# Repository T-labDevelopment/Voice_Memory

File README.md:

# Voice_Memory — 主開発：ESP32 T-Display Rev.A

**2026-11-25時点の主開発対象はESP32 T-Display 16MB版。** CH32V003 v1/v2は履歴として保持します。設計世代や製造用スナップショットは上書きせず区別します。

- [2026-11-25 00:46 Gerber受領・差し替え確認（PCB(2).zipを発注用正本とする）](releases/esp32-tdisplay-orderfiles-check-2026-11-25/ORDER_STATUS_JA.md)
- [2026-11-25 00:39 KiCad設計正本](hardware/source-archives/tdisplay-order-candidate-2026-11-25/VoiceMemory_TDisplay-2026-11-25_003943.zip)
- [2026-11-24 23:41 発注前GPIO検証版](releases/esp32-tdisplay-preorder-pin-audit-2026-11-24/README.md)
- [2026-11-24 旧Prototype発注データ](releases/esp32-tdisplay-prototype-ordered-2026-11-24/README.md)
- [旧CH32V003版の製造履歴](releases/v2-manufacturing-approved-2026-11-11/README.md)

**発注用Gerber正本：** [PCB(2).zip](hardware/source-archives/tdisplay-order-candidate-2026-11-25/PCB(2).zip)（SHA-256は[検査記録](releases/esp32-tdisplay-orderfiles-check-2026-11-25/GERBER_MANIFEST_2026-11-25.json)に記載）。前に受領した `PCB(1).zip` は空であり**使用禁止**。

**2026-11-25 00:56:43 JSTのJLCPCB注文画面で、PCB 5枚・基板代US$2.00・送料US$1.00・合計US$3.00の「支払い済み」および「レビュー」工程を確認。** 基板厚1.2mmはユーザー指定の注文条件で、画像単独では独立照合できません。注文番号は公開リポジトリに掲載しません。KiCad設計ファイルやGerberそのものの厚み設定は変更していません。基板認識寸法はGerberジョブファイル上80.06×100.05mmであり、見積価格・CAM外形・取付穴は注文画面で確認してください。

Git作業ブランチで管理し、`main`へは指示なく統合しません。

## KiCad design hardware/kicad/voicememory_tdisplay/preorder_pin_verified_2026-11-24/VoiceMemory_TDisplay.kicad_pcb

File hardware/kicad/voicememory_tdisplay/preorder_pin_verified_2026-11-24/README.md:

# ESP32 T-Display Rev.A — 2026-11-24 23:41 発注準備版

**User-supplied exact source:** `VoiceMemory_TDisplay-2026-11-24_234138.zip`。

- 状態：発注前GPIO・フットプリント照合済み、外形80.01 × 100.00 mm。基板設計はユーザー修正済み。
- ERC(4).rpt：2026-11-24 23:09 エラー0 / 警告0。
- DRC(2).rpt：2026-11-24 23:41 違反0 / 未接続0 / FPエラー0。
- [24ピン監査と注意事項](PIN_AUDIT_2026-11-24_JA.md)、[ピンごとのCSV](MODULE_PINMAP_AUDIT_2026-11-24.csv)。
- 既存KiCad配置・回路・配線は変更しない。自動保存・個人設定`*.kicad_prl`は作業ディレクトリから除外。
- メーカーPinout照合はLILYGO初代T-Display V1.1を基準とする。TENSTAR16MB版の実品電源ルートおよびピン互換性は購入現物の照合事項。
- 過去版`PCB.zip` は使わず、このPCBからGerber/ドリルを新規出力する。

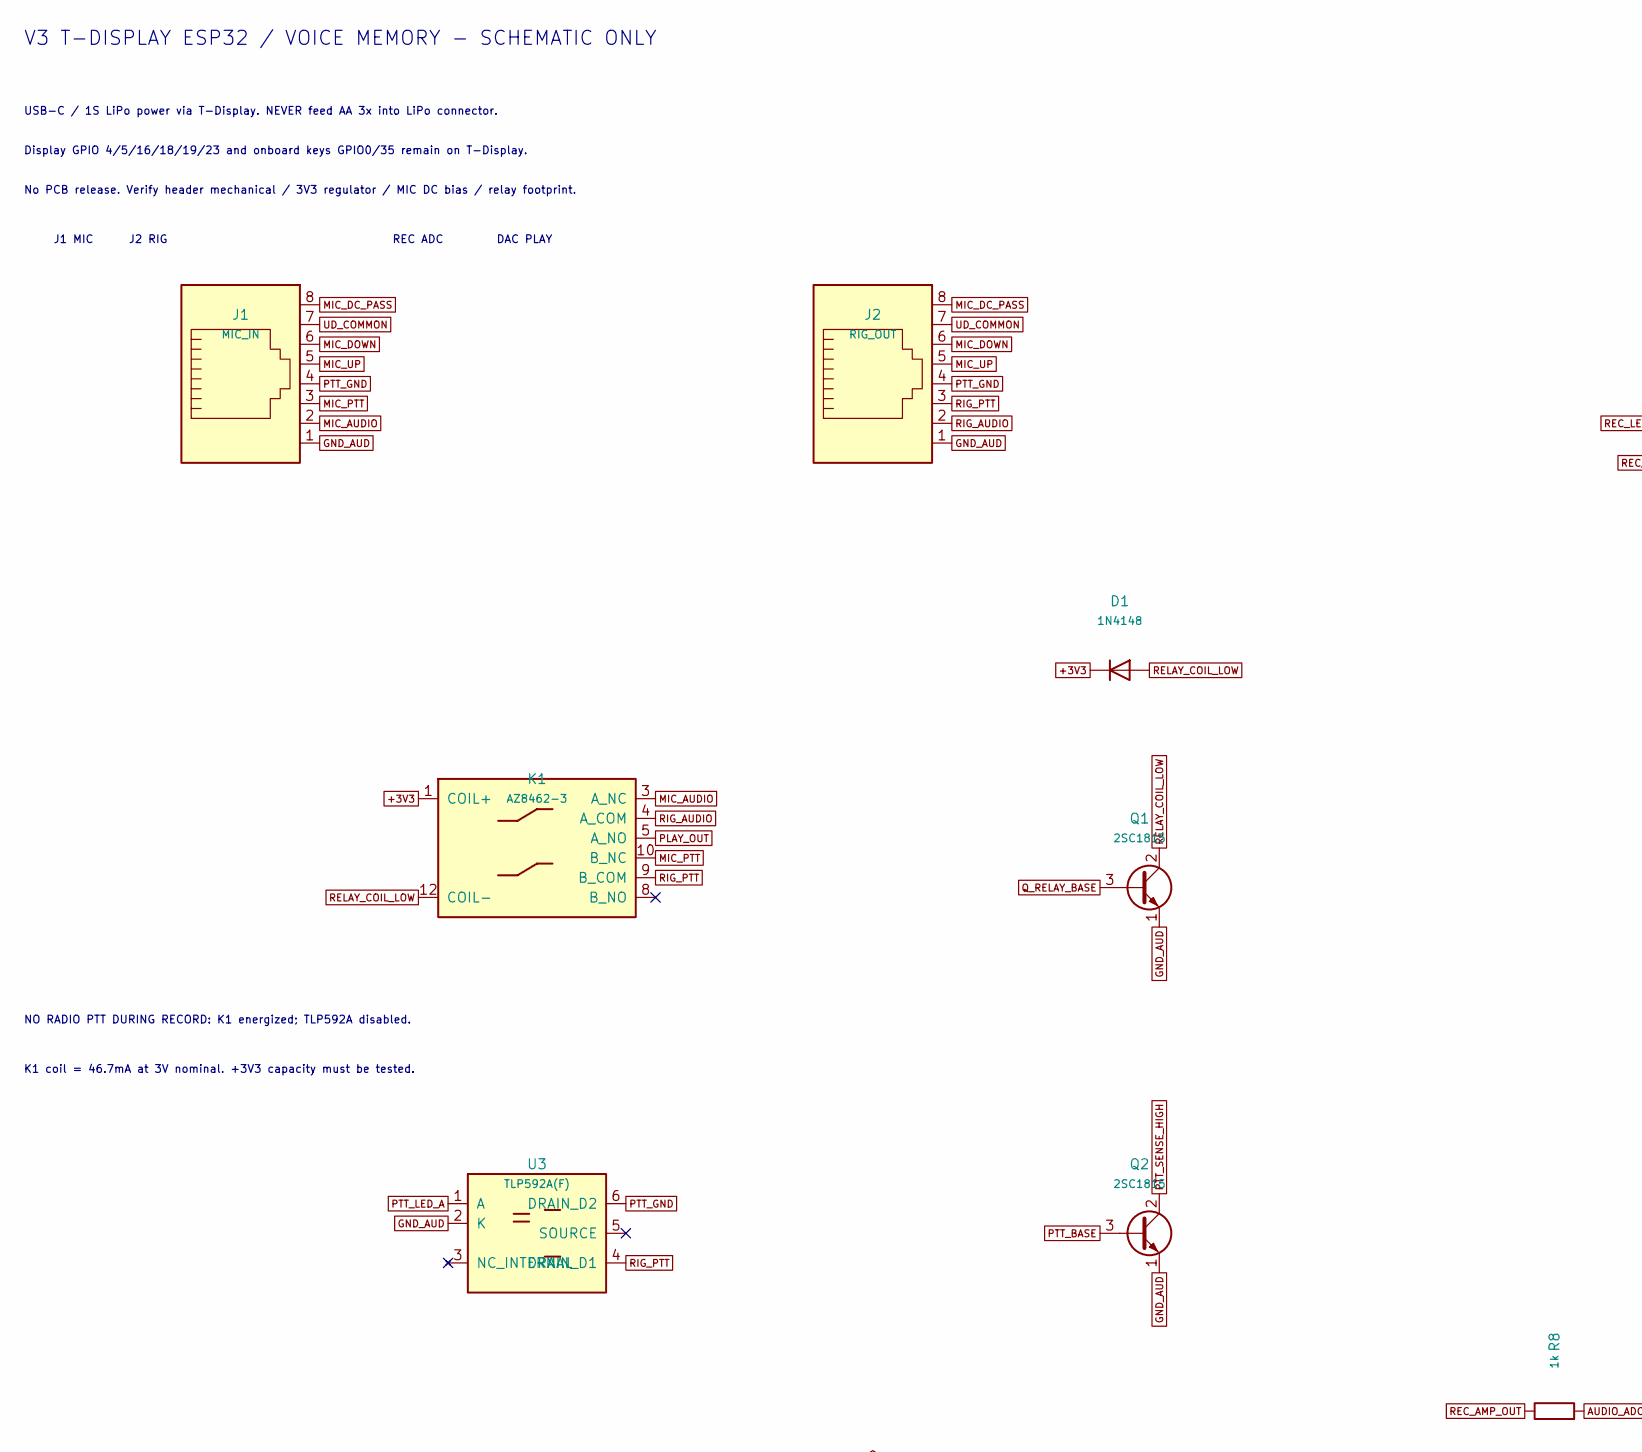
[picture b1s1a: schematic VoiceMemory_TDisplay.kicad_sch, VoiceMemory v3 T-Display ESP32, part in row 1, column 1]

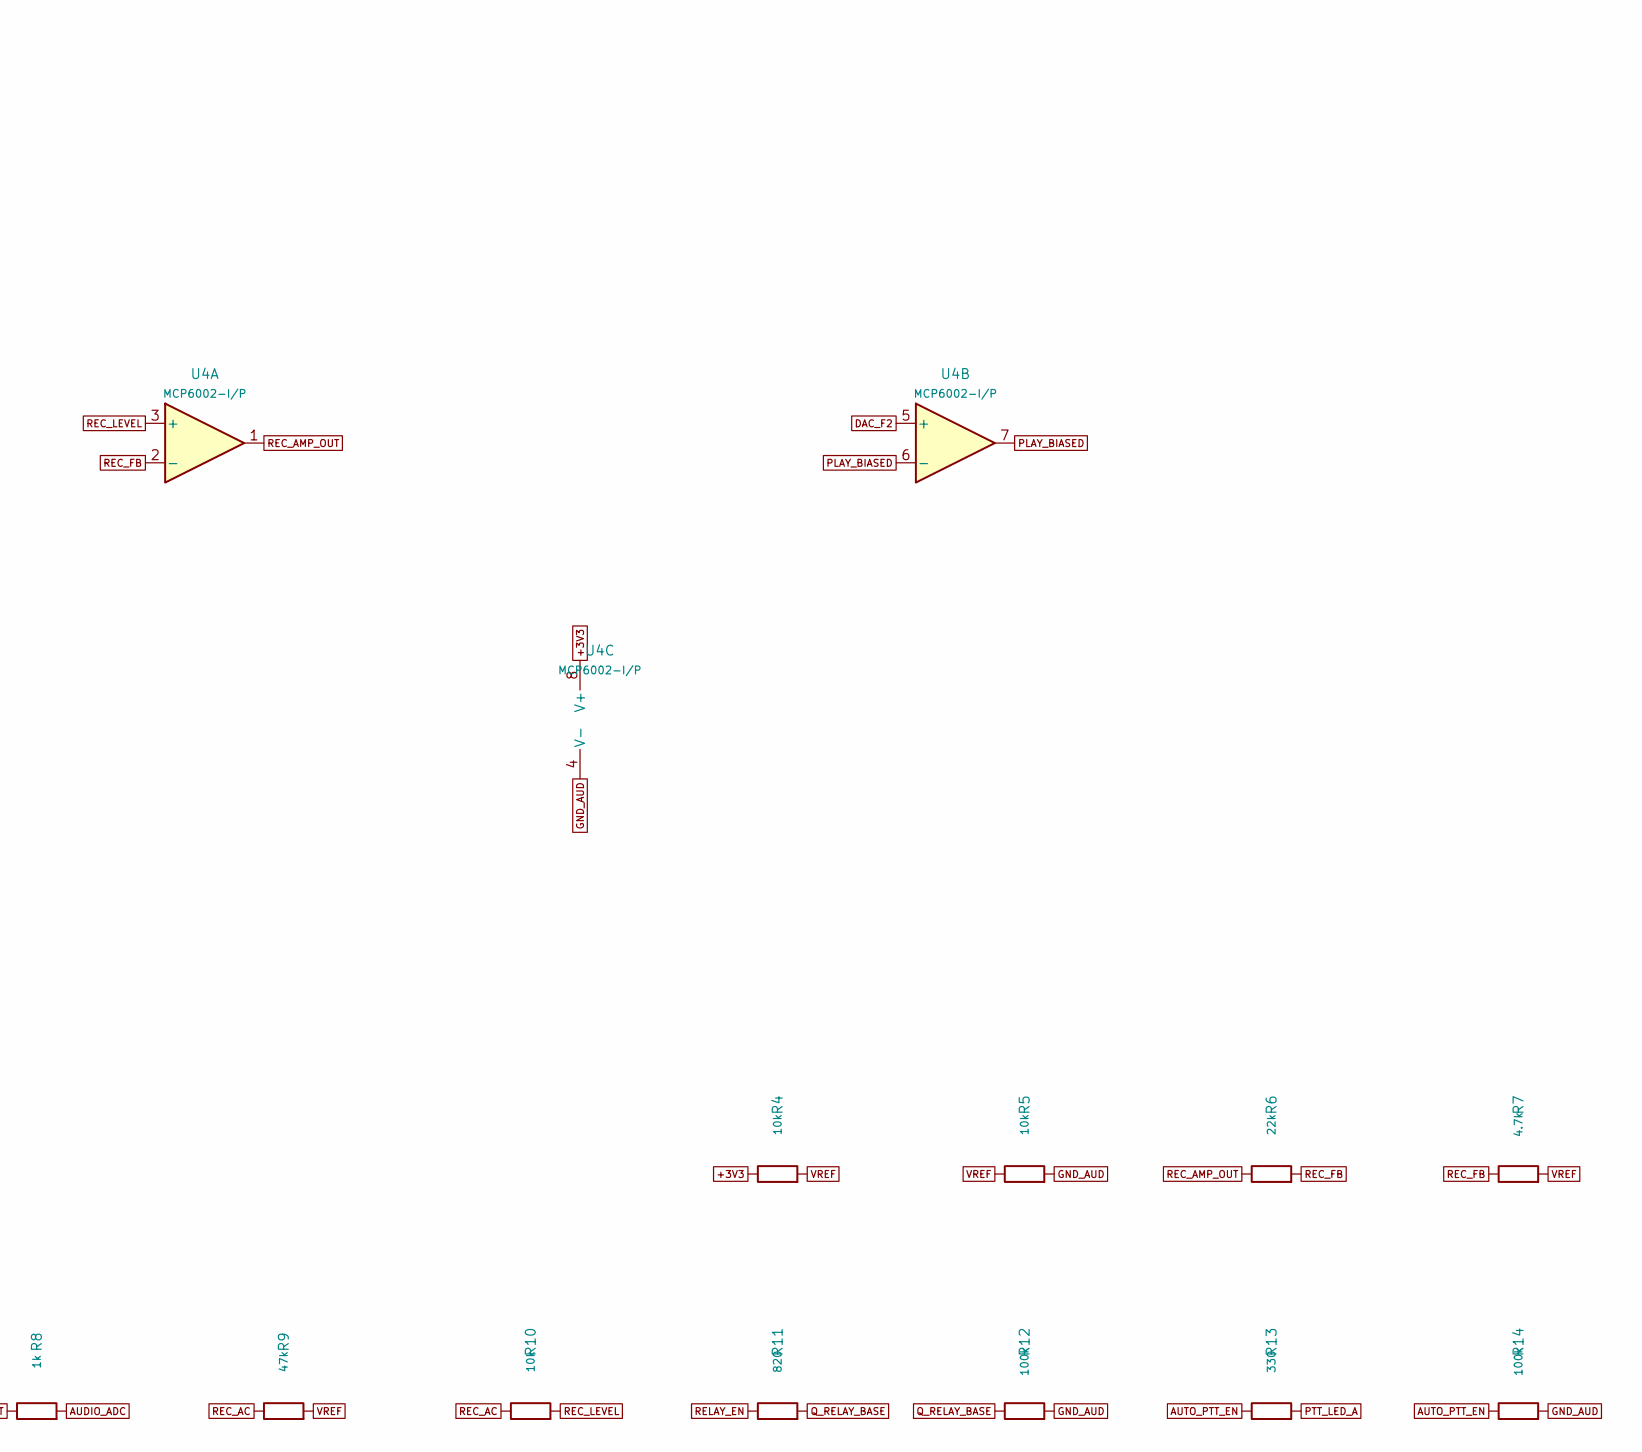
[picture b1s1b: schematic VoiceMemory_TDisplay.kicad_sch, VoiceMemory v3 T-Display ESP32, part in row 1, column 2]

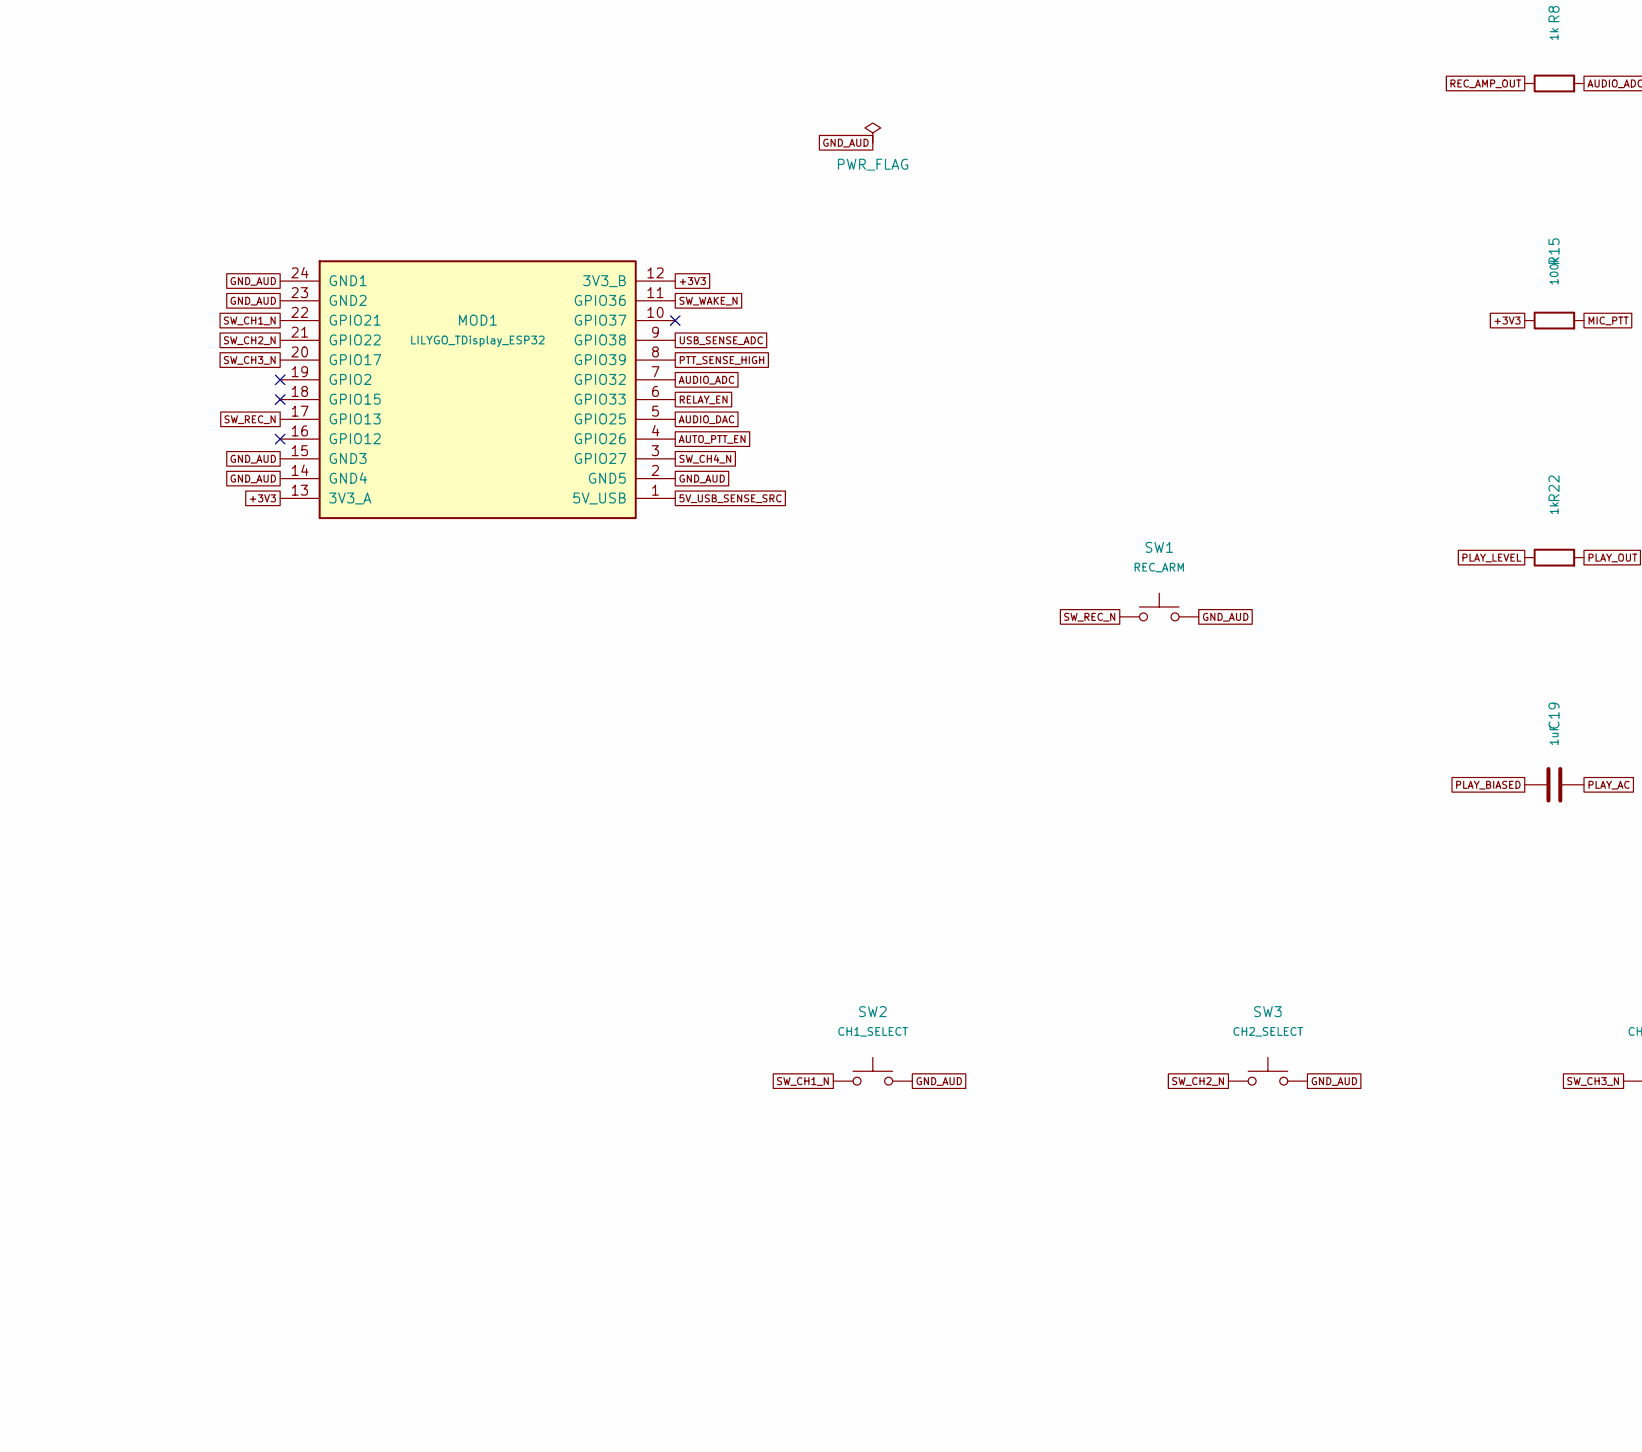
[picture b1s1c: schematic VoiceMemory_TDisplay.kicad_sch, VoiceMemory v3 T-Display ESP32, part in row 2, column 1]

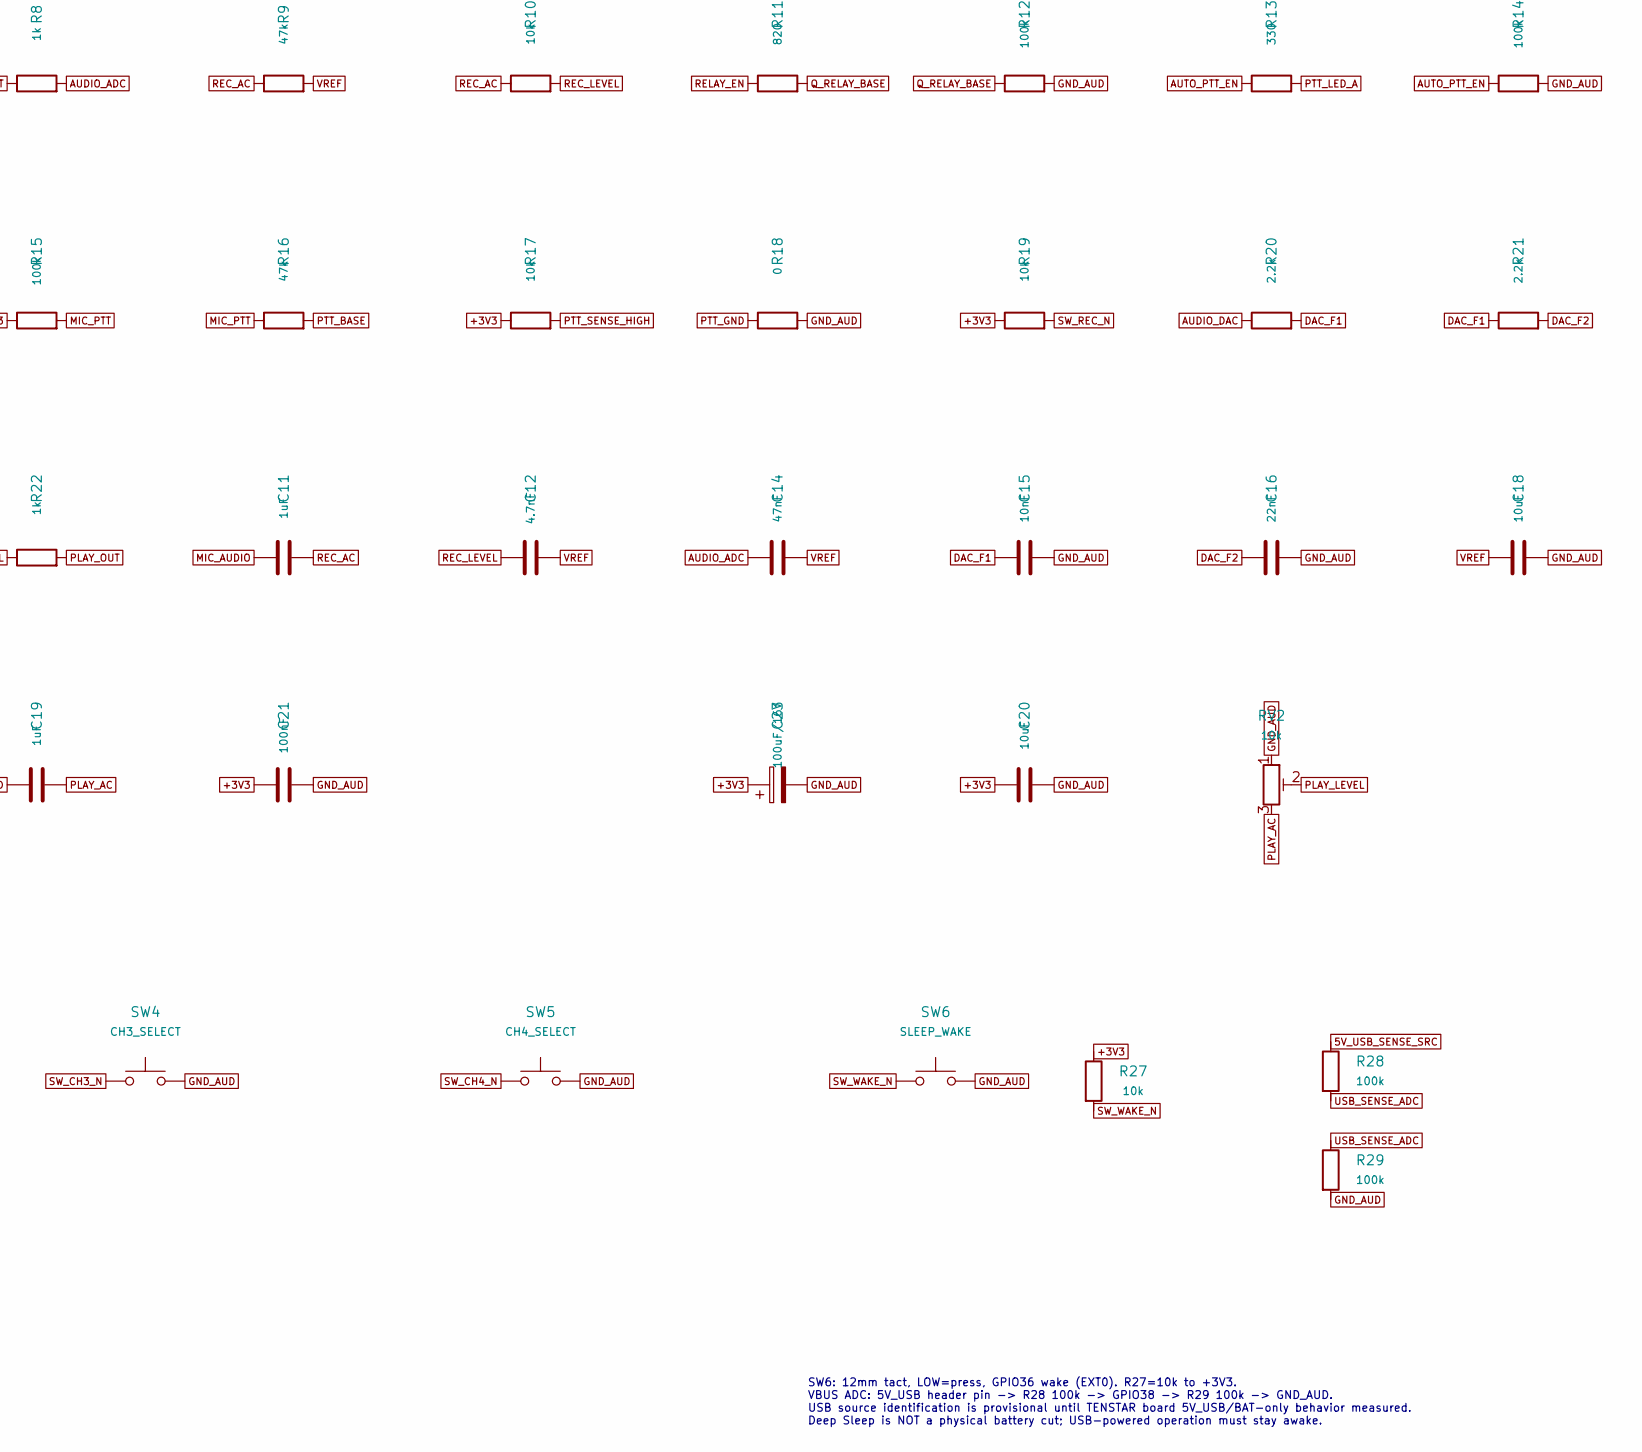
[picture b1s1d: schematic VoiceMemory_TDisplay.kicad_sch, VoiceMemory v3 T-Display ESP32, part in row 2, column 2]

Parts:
C11, C19: 1uF; C_1206_3216Metric; Manufacturer Part Number 25MU105MA23216
C12: 4.7nF; C_0805_2012Metric; Tolerance ±5%; Manufacturer Part Number GRM2195C1H472JA01D
C14: 47nF; C_0805_2012Metric; Tolerance ±5%; Manufacturer Part Number GRM2191X1A473JA01D
C15: 10nF; C_0805_2012Metric; Tolerance ±5%; Manufacturer Part Number GRM2195C1H103JA01D
C16: 22nF; C_0805_2012Metric; Tolerance ±5%; Manufacturer Part Number GRM21B5C1H223JA01L
C18, C20: 10uF; C_0805_2012Metric; Tolerance ±10%; Manufacturer Part Number CL21A106KOQNNNE
C21: 100nF; C_0805_2012Metric; Tolerance ±5%; Manufacturer Part Number GRM21B1X1A104JA01L
C23: 100uF/16V; CP_Radial_D5.0mm_P2.00mm; Tolerance ±20%; Manufacturer Part Number 16PX100MEFC5X11
D1: 1N4148; D_SOD-123
J1: MIC_IN; RJ45_8P8C_THT_15.91x15.10
J2: RIG_OUT; RJ45_8P8C_THT_15.91x15.10
K1: AZ8462-3; Relay_Zettler_AZ8462_DIP8
MOD1: LILYGO_TDisplay_ESP32; TTGO-T-Display
Q1, Q2: 2SC1815; TO-92_Inline
R4, R5, R10, R17, R19, R27: 10k; R_0805_2012Metric
R6: 22k; R_0805_2012Metric
R7: 4.7k; R_0805_2012Metric
R8, R22: 1k; R_0805_2012Metric
R9, R16: 47k; R_0805_2012Metric
R11: 820; R_0805_2012Metric
R12, R14, R15, R28, R29: 100k; R_0805_2012Metric
R13: 330; R_0805_2012Metric
R18: 0; R_0805_2012Metric
R20, R21: 2.2k; R_0805_2012Metric
RV2: 10k; Potentiometer_Runtron_RM-065_Vertical
SW1: REC_ARM; SW_PUSH-12mm
SW2: CH1_SELECT; SW_PUSH-12mm
SW3: CH2_SELECT; SW_PUSH-12mm
SW4: CH3_SELECT; SW_PUSH-12mm
SW5: CH4_SELECT; SW_PUSH-12mm
SW6: SLEEP_WAKE; SW_PUSH-12mm
U3: TLP592A(F); DIP-6_W7.62mm
U4: MCP6002-I/P; DIP-8_W7.62mm

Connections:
5V_USB_SENSE_SRC: MOD1.1 (5V_USB), R28.1
+3V3: C20.1, C21.1, C23.1, D1.1 (K), K1.1 (COIL+), MOD1.12 (3V3_B), MOD1.13 (3V3_A), R4.1, R15.1, R17.1, R19.1, R27.1, U4.8 (V+)
AUDIO_ADC: C14.1, MOD1.7 (GPIO32), R8.2
AUDIO_DAC: MOD1.5 (GPIO25), R20.1
AUTO_PTT_EN: MOD1.4 (GPIO26), R13.1, R14.1
DAC_F1: C15.1, R20.2, R21.1
DAC_F2: C16.1, R21.2, U4.5 (+)
GND_AUD: C15.2, C16.2, C18.2, C20.2, C21.2, C23.2, J1.1, J2.1, MOD1.2 (GND5), MOD1.14 (GND4), MOD1.15 (GND3), MOD1.23 (GND2), MOD1.24 (GND1), Q1.1 (E), Q2.1 (E), R5.2, R12.2, R14.2, R18.2, R29.2, RV2.1, SW1.2, SW2.2, SW3.2, SW4.2, SW5.2, SW6.2, U3.2 (K), U4.4 (V-)
MIC_AUDIO: C11.1, J1.2, K1.3 (A_NC)
MIC_DC_PASS: J1.8, J2.8
MIC_DOWN: J1.6, J2.6
MIC_PTT: J1.3, K1.10 (B_NC), R15.2, R16.1
MIC_UP: J1.5, J2.5
PLAY_AC: C19.2, RV2.3
PLAY_BIASED: C19.1, U4.6 (-), U4.7
PLAY_LEVEL: R22.1, RV2.2
PLAY_OUT: K1.5 (A_NO), R22.2
PTT_BASE: Q2.3 (B), R16.2
PTT_GND: J1.4, J2.4, R18.1, U3.6 (DRAIN_D2)
PTT_LED_A: R13.2, U3.1 (A)
PTT_SENSE_HIGH: MOD1.8 (GPIO39), Q2.2 (C), R17.2
Q_RELAY_BASE: Q1.3 (B), R11.2, R12.1
REC_AC: C11.2, R9.1, R10.1
REC_AMP_OUT: R6.1, R8.1, U4.1
REC_FB: R6.2, R7.1, U4.2 (-)
REC_LEVEL: C12.1, R10.2, U4.3 (+)
RELAY_COIL_LOW: D1.2 (A), K1.12 (COIL-), Q1.2 (C)
RELAY_EN: MOD1.6 (GPIO33), R11.1
RIG_AUDIO: J2.2, K1.4 (A_COM)
RIG_PTT: J2.3, K1.9 (B_COM), U3.4 (DRAIN_D1)
SW_CH1_N: MOD1.22 (GPIO21), SW2.1
SW_CH2_N: MOD1.21 (GPIO22), SW3.1
SW_CH3_N: MOD1.20 (GPIO17), SW4.1
SW_CH4_N: MOD1.3 (GPIO27), SW5.1
SW_REC_N: MOD1.17 (GPIO13), R19.2, SW1.1
SW_WAKE_N: MOD1.11 (GPIO36), R27.2, SW6.1
UD_COMMON: J1.7, J2.7
USB_SENSE_ADC: MOD1.9 (GPIO38), R28.2, R29.1
VREF: C12.2, C14.2, C18.1, R4.2, R5.1, R7.2, R9.2

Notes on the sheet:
No PCB release. Verify header mechanical / 3V3 regulator / MIC DC bias / relay footprint.
K1 coil = 46.7mA at 3V nominal. +3V3 capacity must be tested.
SW6: 12mm tact, LOW=press, GPIO36 wake (EXT0). R27=10k to +3V3. VBUS ADC: 5V_USB header pin -> R28 100k -> GPIO38 -> R29 100k -> GND_AUD. USB source identification is provisional until TENSTAR board 5V_USB/BAT-only behavior measured. Deep Sleep is NOT a physical battery cut; USB-powered operation m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
J1 MIC J2 RIG REC ADC DAC PLAY
USB-C / 1S LiPo power via T-Display. NEVER feed AA 3x into LiPo connector.
V3 T-DISPLAY ESP32 / VOICE MEMORY - SCHEMATIC ONLY
NO RADIO PTT DURING RECORD: K1 energized; TLP592A disabled.
Display GPIO 4/5/16/18/19/23 and onboard keys GPIO0/35 remain on T-Display.

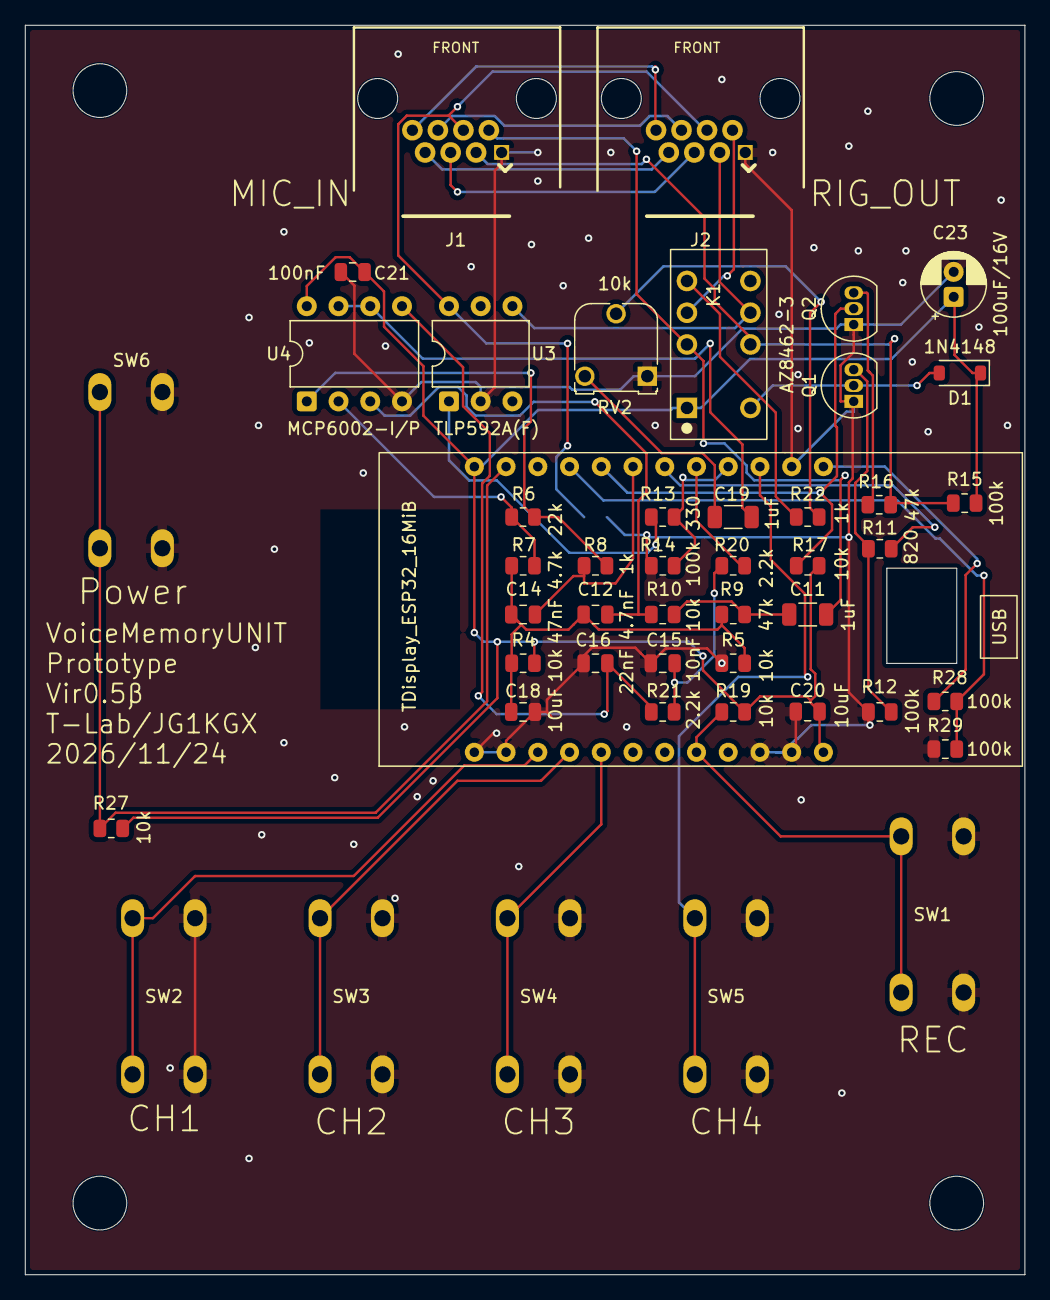
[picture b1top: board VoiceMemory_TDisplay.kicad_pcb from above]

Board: 2 copper layers, 80.0 x 100.0 mm, 48 parts (1 on the bottom side), 39 nets.

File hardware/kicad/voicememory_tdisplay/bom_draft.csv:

Ref,Part,Value,Qty,Footprint,Status
"J1","Connector:RJ45","MIC_IN","1","Voice_Memory:RJ45_8P8C_THT_15.91x15.10","VERIFY_MATCH"
"J2","Connector:RJ45","RIG_OUT","1","Voice_Memory:RJ45_8P8C_THT_15.91x15.10","VERIFY_MATCH"
"K1","Voice_Memory:AZ8462-3","AZ8462-3","1","VoiceMemory_TDisplay:Relay_Zettler_AZ8462_DIP8","VERIFY_MATCH"
"U3","Voice_Memory:TLP592A","TLP592A(F)","1","Package_DIP:DIP-6_W7.62mm","VERIFY_MATCH"
"MOD1","VoiceMemory_TDisplay:TDisplay_ESP32_V1","LILYGO_TDisplay_ESP32","1","VoiceMemory_TDisplay:TTGO-T-Display","SCHEMATIC_ONLY"
"U2","Voice_Memory:W25Q32RVCSJM","W25Q32RVCSJM","1","Package_SO:SOP-8_5.28x5.23mm_P1.27mm","VERIFY_MATCH"
"SW1","Switch:SW_Push","REC_ARM","1","Button_Switch_THT:SW_PUSH_6mm_H4.3mm","VERIFY_MATCH"
"U4","Amplifier_Operational:MCP6002-xP","MCP6002-I/P","1","Package_DIP:DIP-8_W7.62mm","VERIFY_MATCH"
"Q1","Transistor_BJT:Q_NPN_ECB","2SC1815","1","Package_TO_SOT_THT:TO-92_Inline","VERIFY_MATCH"
"Q2","Transistor_BJT:Q_NPN_ECB","2SC1815","1","Package_TO_SOT_THT:TO-92_Inline","VERIFY_MATCH"
"D1","Voice_Memory:D_1N4148_VM","1N4148","1","Diode_SMD:D_SOD-123","VERIFY_MATCH"
"R1","Device:R","10k","1","Resistor_SMD:R_0805_2012Metric","VERIFY_MATCH"
"R2","Device:R","10k","1","Resistor_SMD:R_0805_2012Metric","VERIFY_MATCH"
"R3","Device:R","10k","1","Resistor_SMD:R_0805_2012Metric","VERIFY_MATCH"
"R4","Device:R","10k","1","Resistor_SMD:R_0805_2012Metric","VERIFY_MATCH"
"R5","Device:R","10k","1","Resistor_SMD:R_0805_2012Metric","VERIFY_MATCH"
"R6","Device:R","22k","1","Resistor_SMD:R_0805_2012Metric","VERIFY_MATCH"
"R7","Device:R","4.7k","1","Resistor_SMD:R_0805_2012Metric","VERIFY_MATCH"
"R8","Device:R","1k","1","Resistor_SMD:R_0805_2012Metric","VERIFY_MATCH"
"R9","Device:R","47k","1","Resistor_SMD:R_0805_2012Metric","VERIFY_MATCH"
"R10","Device:R","10k","1","Resistor_SMD:R_0805_2012Metric","VERIFY_MATCH"
"R11","Device:R","820","1","Resistor_SMD:R_0805_2012Metric","VERIFY_MATCH"
"R12","Device:R","100k","1","Resistor_SMD:R_0805_2012Metric","VERIFY_MATCH"
"R13","Device:R","330","1","Resistor_SMD:R_0805_2012Metric","VERIFY_MATCH"
"R14","Device:R","100k","1","Resistor_SMD:R_0805_2012Metric","VERIFY_MATCH"
"R15","Device:R","100k","1","Resistor_SMD:R_0805_2012Metric","VERIFY_MATCH"
"R16","Device:R","47k","1","Resistor_SMD:R_0805_2012Metric","VERIFY_MATCH"
"R17","Device:R","10k","1","Resistor_SMD:R_0805_2012Metric","VERIFY_MATCH"
"R18","Device:R","0","1","Resistor_SMD:R_0805_2012Metric","VERIFY_MATCH"
"R19","Device:R","10k","1","Resistor_SMD:R_0805_2012Metric","VERIFY_MATCH"
"R20","Device:R","2.2k","1","Resistor_SMD:R_0805_2012Metric","VERIFY_MATCH"
"R21","Device:R","2.2k","1","Resistor_SMD:R_0805_2012Metric","VERIFY_MATCH"
"R22","Device:R","1k","1","Resistor_SMD:R_0805_2012Metric","VERIFY_MATCH"
"C11","Device:C","1uF","1","Capacitor_SMD:C_0805_2012Metric","VERIFY_MATCH"
"C12","Device:C","4.7nF","1","Capacitor_SMD:C_0805_2012Metric","VERIFY_MATCH"
"C14","Device:C","47nF","1","Capacitor_SMD:C_0805_2012Metric","VERIFY_MATCH"
"C15","Device:C","10nF","1","Capacitor_SMD:C_0805_2012Metric","VERIFY_MATCH"
"C16","Device:C","22nF","1","Capacitor_SMD:C_0805_2012Metric","VERIFY_MATCH"
"C18","Device:C","10uF","1","Capacitor_SMD:C_0805_2012Metric","VERIFY_MATCH"
"C19","Device:C","1uF","1","Capacitor_SMD:C_0805_2012Metric","VERIFY_MATCH"
"C21","Device:C","100nF","1","Capacitor_SMD:C_0805_2012Metric","VERIFY_MATCH"
"C22","Device:C","100nF","1","Capacitor_SMD:C_0805_2012Metric","VERIFY_MATCH"
"C23","Device:C_Polarized","100uF/6.3V","1","Capacitor_THT:CP_Radial_D5.0mm_P2.00mm","VERIFY_MATCH"
"C20","Device:C","10uF","1","Capacitor_SMD:C_0805_2012Metric","VERIFY_MATCH"
"RV2","Voice_Memory:R_Potentiometer_Trim_VM","10k","1","Potentiometer_THT:Potentiometer_Runtron_RM-065_Vertical","VERIFY_MATCH"

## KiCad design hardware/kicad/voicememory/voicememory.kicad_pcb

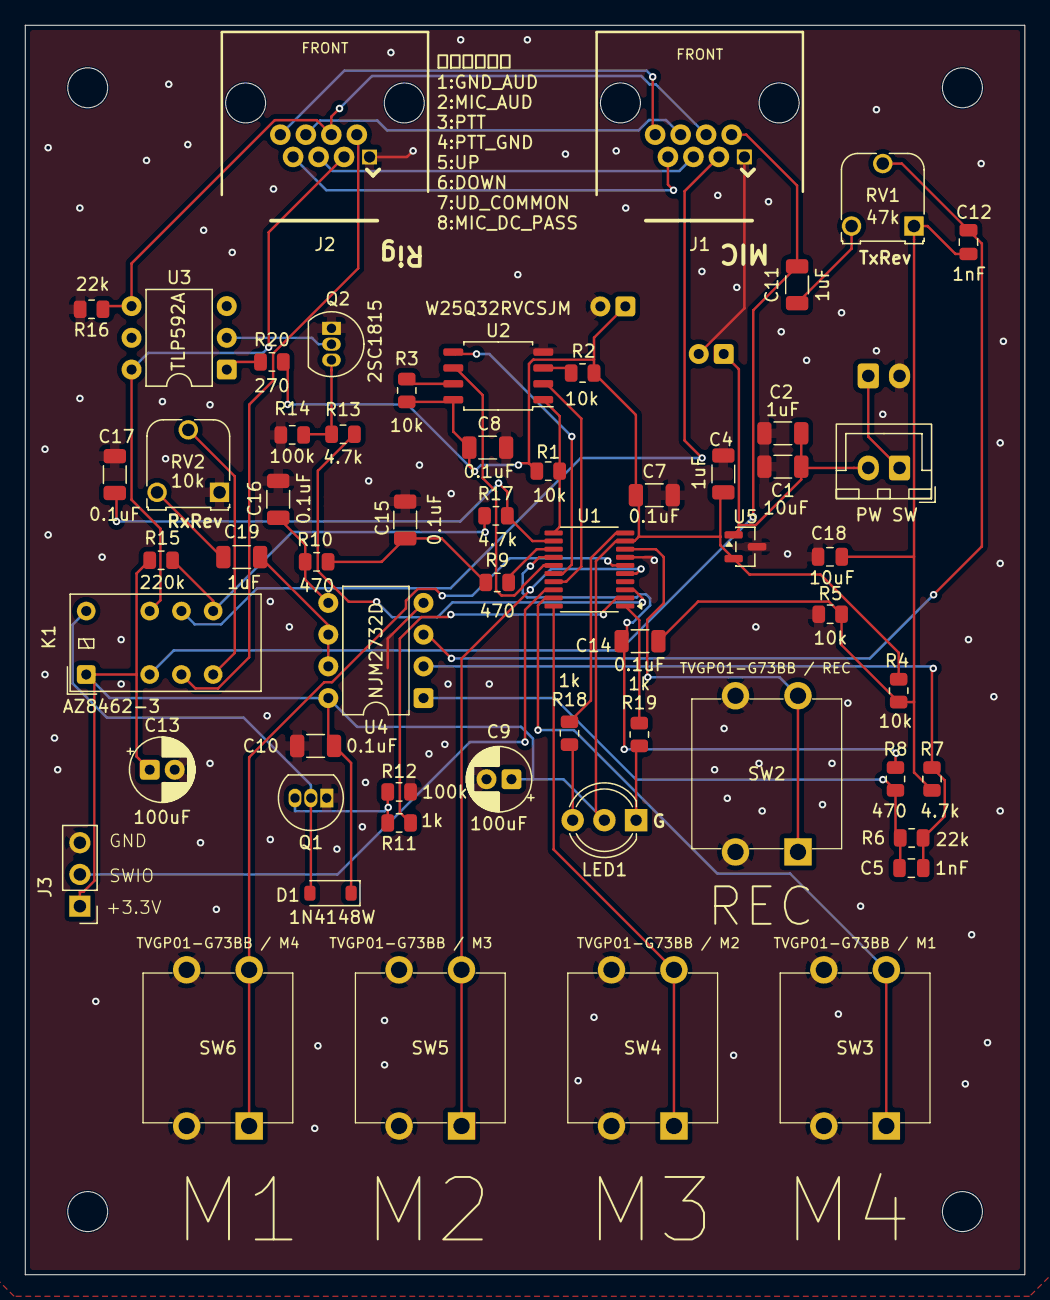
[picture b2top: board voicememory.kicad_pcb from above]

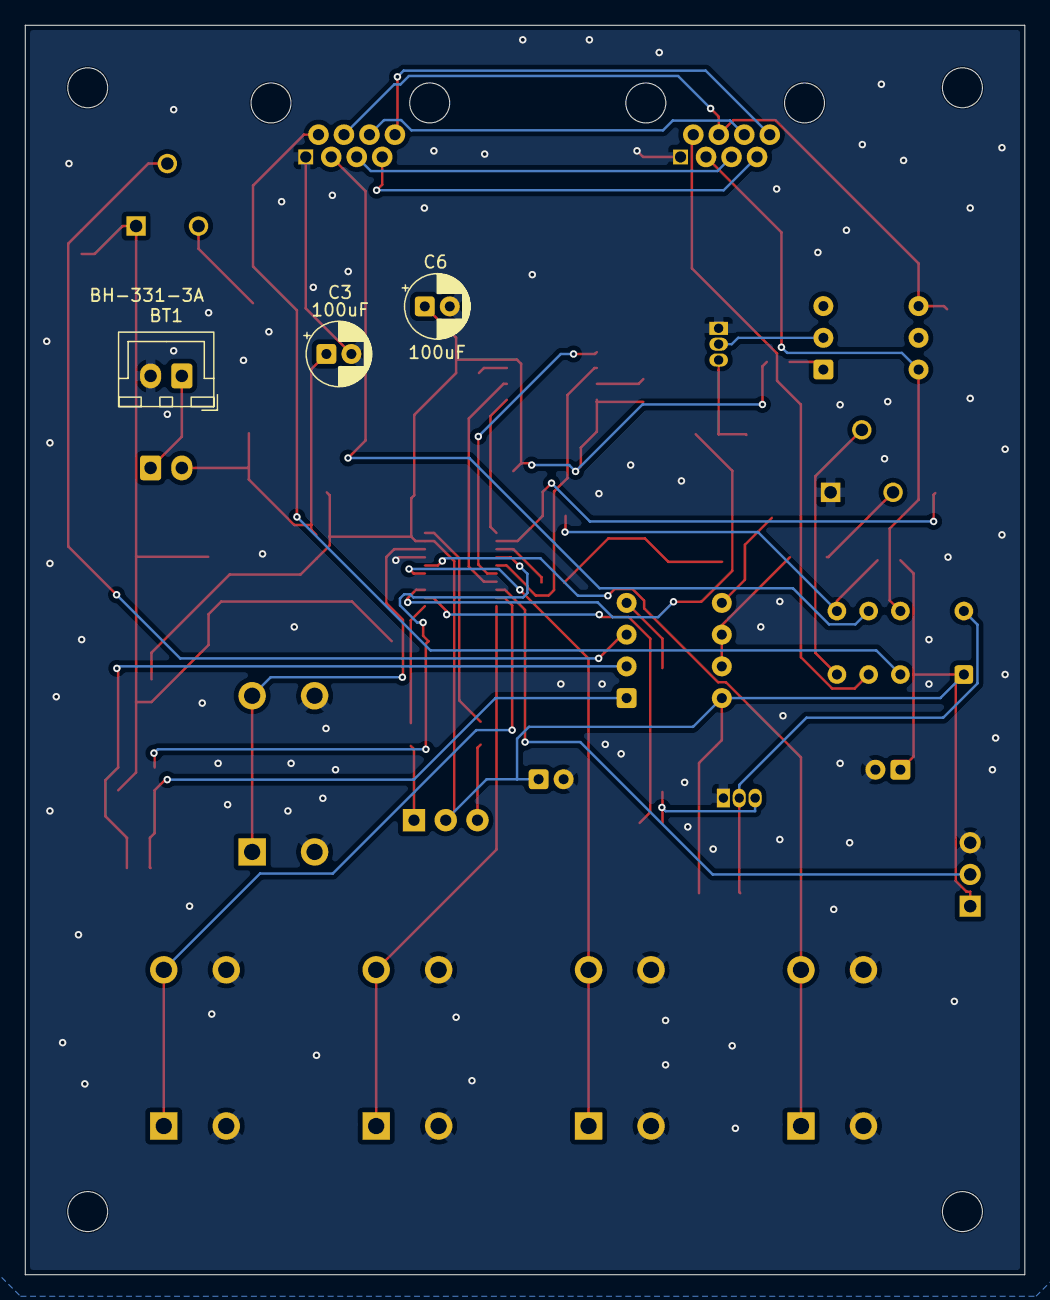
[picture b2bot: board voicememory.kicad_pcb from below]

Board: 2 copper layers, 80.0 x 100.0 mm, 61 parts (3 on the bottom side), 50 nets.

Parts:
BT1: BH-331-3A; JST_XH_B2B-XH-A_1x02_P2.50mm_Vertical
C1: 10uF; C_1206_3216Metric
C2, C4, C11, C19: 1uF; C_1206_3216Metric
C3, C6, C9, C13: 100uF; CP_Radial_D5.0mm_P2.00mm
C5, C12: 1nF; C_0805_2012Metric
C7, C8, C10, C14, C15, C16, C17: 0.1uF; C_1206_3216Metric
C18: 10uF; C_0805_2012Metric
D1: 1N4148W; D_SOD-123
J1: RJ45_8P8C MIC; RJ45_8P8C_THT_15.91x15.10
J2: RJ45_8P8C RIG; RJ45_8P8C_THT_15.91x15.10
J3: WCH-Link 3P; PinHeader_1x03_P2.54mm_Vertical
K1: AZ8462-3; Relay_DPDT_Kemet_EC2_NU
LED1: LT6CU7R; LED_D5.0mm-3
Q1: 2SC1815L-Y-T92; TO-92_Inline
Q2: 2SC1815; TO-92_Inline
R1, R2, R3, R4, R5: 10k; R_0805_2012Metric
R6, R16: 22k; R_0805_2012Metric
R7, R13, R17: 4.7k; R_0805_2012Metric
R8, R9, R10: 470; R_0805_2012Metric
R11, R18, R19: 1k; R_0805_2012Metric
R12, R14: 100k; R_0805_2012Metric
R15: 220k; R_0805_2012Metric
R20: 270; R_0805_2012Metric
RV1: 47k; Potentiometer_Runtron_RM-065_Vertical
RV2: 10k; Potentiometer_Runtron_RM-065_Vertical
SW1: CW-SB11KKFF; JST_XH_B2B-XH-A_1x02_P2.50mm_Vertical
SW2: TVGP01-G73BB / REC; SW_TVGP01_G73BB_12mm
SW3: TVGP01-G73BB / M1; SW_TVGP01_G73BB_12mm
SW4: TVGP01-G73BB / M2; SW_TVGP01_G73BB_12mm
SW5: TVGP01-G73BB / M3; SW_TVGP01_G73BB_12mm
SW6: TVGP01-G73BB / M4; SW_TVGP01_G73BB_12mm
U1: CH32V003F4P6; TSSOP-20_4.4x6.5mm_P0.65mm
U2: W25Q32RVCSJM; SOP-8_5.28x5.23mm_P1.27mm
U3: TLP592A; DIP-6_W7.62mm
U4: NJM2732D; DIP-8_W7.62mm
U5: AP7333-33SAG; SOT-23

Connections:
+3V3: C4.1, C6.1, C7.1, C8.1, C9.1, C10.1, C13.1, D1.1 (K), J3.1, K1.1 (COIL+), LED1.2 (A_COMMON), R1.2, R2.2, R3.2, R4.1, R15.1, R20.1, U1.9 (VDD), U2.8 (VCC), U4.8 (V+), U5.2 (OUT)
AQV_LED_A: R20.2, U3.1 (A)
AQV_LED_K: Q2.2 (C), U3.2 (K)
AUDIO_ADC: C14.1, R8.2, U1.14 (PC4)
AUDIO_PWM: R9.1, U1.13 (PC3)
AUTO_PTT_EN: R13.1, U1.3 (PD6)
FLASH_CS: R1.1, U1.11 (PC1), U2.1 (/CS)
FLASH_HOLD_N: R3.1, U2.7 (/HOLD/IO3)
FLASH_WP_N: R2.1, U2.3 (/WP/IO2)
GND_AUD: BT1.2 (-), C1.2, C2.2, C3.2, C4.2, C6.2, C7.2, C8.2, C9.2, C10.2, C13.2, C15.2, C16.2, C17.2, C18.2, J1.1, J2.1, J3.3, Q1.1 (E), Q2.1 (E), R5.2, R12.2, R14.2, R16.2, RV2.1, SW2.2, SW3.2, SW4.2, SW5.2, SW6.2, U1.7 (VSS), U2.4 (GND), U4.4 (V-), U5.3 (GND)
LED_G: R19.2, U1.1 (PD4)
LED_G_K: LED1.1 (K_YG), R19.1
LED_R: R18.2, U1.10 (PC0)
LED_R_K: LED1.3 (K_RED), R18.1
MIC_AUDIO: C11.1, J1.2, K1.3 (A_NC)
MIC_DC_PASS: J1.8, J2.8
MIC_DOWN: J1.6, J2.6
MIC_PTT: J1.3, K1.9 (B_COM)
MIC_UP: J1.5, J2.5
PLAY_AC: C19.2, RV2.3
PLAY_BIASED: C19.1, U4.6 (-), U4.7
PLAY_OUT: K1.5 (A_NO), RV2.2
PTT_GND: J1.4, J2.4, R16.1, U3.4 (DRAIN_D1)
PTT_SENSE_LOCAL: K1.8 (B_NO), R15.2, R17.1
PTT_SENSE_MCU: C17.1, R17.2, U1.12 (PC2)
PWM_F1: C15.1, R9.2, R10.1
PWM_F2: C16.1, R10.2, U4.5 (+)
Q1_BASE: Q1.3 (B), R11.2, R12.1
Q2_BASE: Q2.3 (B), R13.2, R14.1
REC_AC: C11.2, RV1.3
REC_AMP_OUT: C5.1, R6.1, R8.1, U4.1
REC_FB: C5.2, R6.2, R7.1, U4.2 (-)
REC_LEVEL: C12.1, RV1.2, U4.3 (+)
RELAY_COIL_LOW: D1.2 (A), K1.12 (COIL-), Q1.2 (C)
RELAY_EN: R11.1, U1.2 (PD5)
RIG_AUDIO: J2.2, K1.4 (A_COM)
RIG_PTT: J2.3, K1.10 (B_NC), U3.6 (DRAIN_D2)
SPI_MISO: U1.17 (PC7), U2.2 (DO/IO1)
SPI_MOSI: U1.16 (PC6), U2.5 (DI/IO0)
SPI_SCK: U1.15 (PC5), U2.6 (CLK)
SWIO: J3.2, U1.18 (PD1/SWIO)
SW_M1_N: SW3.1, U1.19 (PD2)
SW_M2_N: SW4.1, U1.20 (PD3)
SW_M3_N: SW5.1, U1.5 (PA1)
SW_M4_N: SW6.1, U1.6 (PA2)
SW_REC_N: SW2.1, U1.8 (PD0)
UD_COMMON: J1.7, J2.7
VBAT_RAW: BT1.1 (+), SW1.1 (A)
VBAT_SW: C1.1, C2.1, C3.1, SW1.2 (B), U5.1 (IN)
VREF: C12.2, C14.2, C18.1, R4.2, R5.1, R7.2, RV1.1
